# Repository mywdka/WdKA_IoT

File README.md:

# WdKA_IoT
WdKA Internet of Things Repository

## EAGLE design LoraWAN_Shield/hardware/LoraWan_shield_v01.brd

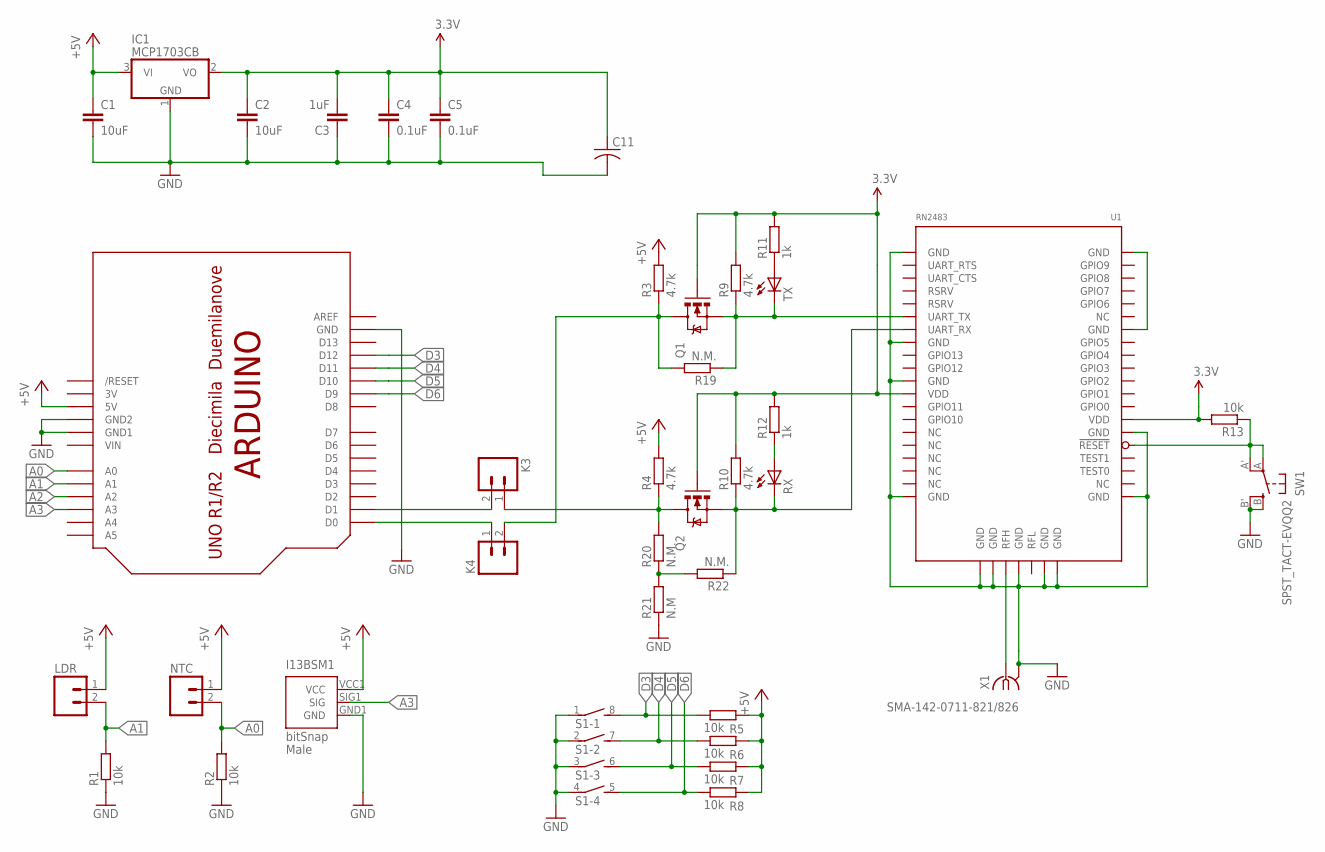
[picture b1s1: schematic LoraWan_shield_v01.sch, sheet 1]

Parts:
ARD1: ARDUINO-NOHOLE
C1, C2: 10uF; C0603K
C3: 1uF; C0603K
C4, C5: 0.1uF; C0603K
C11: C-USC0603; C0603
I13BSM1: BITSNAP_V03_MALE
IC1: MCP1703CB; SOT23
K3, K4: M02LOCK_LONGPADS; 1X02_LOCK_LONGPADS
LDR: M02LOCK_LONGPADS; 1X02_LOCK_LONGPADS
NTC: M02LOCK_LONGPADS; 1X02_LOCK_LONGPADS
Q1, Q2: DMG1012T; SOT523
R1, R2, R5, R6, R7, R8, R13: 10k; R0603
R3, R4, R9, R10: 4.7k; R0603
R11, R12: 1k; R0603
R19, R20, R22: N.M.; R0603
R21: N.M; R0603
RX: LEDCHIPLED_0603; CHIPLED_0603
S1: DIP04S
SW1: SPST_TACT-EVQQ2; EVQ-Q2
TX: LEDCHIPLED_0603; CHIPLED_0603
U1: RN2483
X1: SMA-142-0711-821/826; J502-ND-142-0711-821/826

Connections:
3.3V: C2.1, C3.2, C4.1, C5.1, C11.1, IC1.2 (VO), Q1.1 (G), Q2.1 (G), R9.2, R10.2, R11.2, R12.2, R13.2, U1.12 (VDD), U1.34 (VDD)
3V: ARD1.3V
+5V: ARD1.5V, C1.1, I13BSM1.VCC1 (VCC), IC1.3 (VI), LDR.1, NTC.1, R3.2, R4.2, R5.2, R6.2, R7.2, R8.2; also elsewhere on the board
A0: ARD1.A0, NTC.2, R2.2
A1: ARD1.A1, LDR.2, R1.2
A2: ARD1.A2; also elsewhere on the board
A3: ARD1.A3, I13BSM1.SIG1 (SIG)
ARD_RX: ARD1.D1, K3.2
ARD_TX: ARD1.D0, K4.1
D3: ARD1.D12, R5.1, S1.8 (2)
D4: ARD1.D11, R6.1, S1.7 (2)
D5: ARD1.D10, R7.1, S1.6 (2)
D6: ARD1.D9, R8.1, S1.5 (2)
GND: ARD1.GND, ARD1.GND1, ARD1.GND2, C1.2, C2.2, C3.1, C4.2, C5.2, C11.2, I13BSM1.GND1 (GND), IC1.1 (GND), R1.1, R2.1, R21.1, S1.1, S1.2 (1), S1.3 (1), S1.4 (1), SW1.B (S), SW1.B' (S1), U1.1 (GND), U1.8 (GND), U1.11 (GND), U1.20 (GND), U1.21 (GND), U1.22 (GND), U1.24 (GND), U1.26 (GND), U1.27 (GND), U1.28 (GND), U1.33 (GND), X1.G@1 (2), X1.G@2 (2), X1.G@3 (2), X1.G@4 (2); also elsewhere on the board
unnamed: U1.41 (GND), U1.47 (GND)
unnamed: R13.1, SW1.A, SW1.A' (P1), U1.32 (!RESET!)
unnamed: Q1.2 (S), R9.1, R19.1, TX.C, U1.6 (UART_TX)
unnamed: K4.2, Q1.3 (D), R3.1, R19.2
unnamed: R11.1, TX.A
unnamed: K3.1, Q2.3 (D), R4.1, R20.2
unnamed: R12.1, RX.A
unnamed: U1.23 (RFH), X1.1
unnamed: Q2.2 (S), R10.1, R22.1, RX.C, U1.7 (UART_RX)
unnamed: R20.1, R21.2, R22.2
VIN: ARD1.VIN

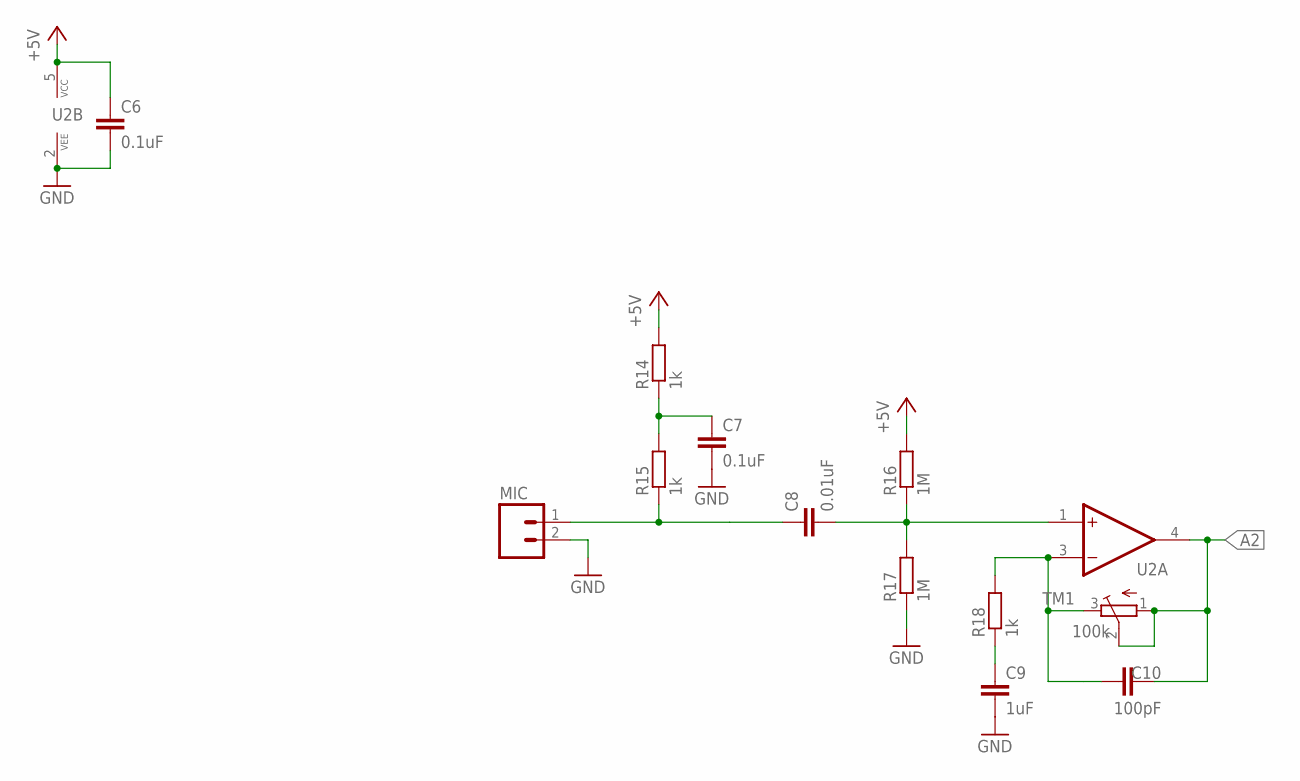
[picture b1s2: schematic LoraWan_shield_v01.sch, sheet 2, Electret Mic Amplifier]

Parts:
C6, C7: 0.1uF; C0603K
C8: 0.01uF; C0603K
C9: 1uF; C0603K
C10: 100pF; C0603K
MIC: M02LOCK_LONGPADS; 1X02_LOCK_LONGPADS
R14, R15, R18: 1k; R0603
R16, R17: 1M; R0603
TM1: 100k; TC33X
U2: MAX4466EXK+T; SC70

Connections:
+5V: C6.1, R14.2, R16.2, U2.5 (VCC); also elsewhere on the board
A2: C10.2, TM1.1 (A), TM1.2 (S), U2.4 (OUT); also elsewhere on the board
GND: C6.2, C7.2, C9.2, MIC.2, R17.1, U2.2 (VEE); also elsewhere on the board
unnamed: C8.1, MIC.1, R15.1
unnamed: C7.1, R14.1, R15.2
unnamed: C9.1, R18.1
unnamed: C8.2, R16.1, R17.2, U2.1 (+IN)
unnamed: C10.1, R18.2, TM1.3 (E), U2.3 (-IN)

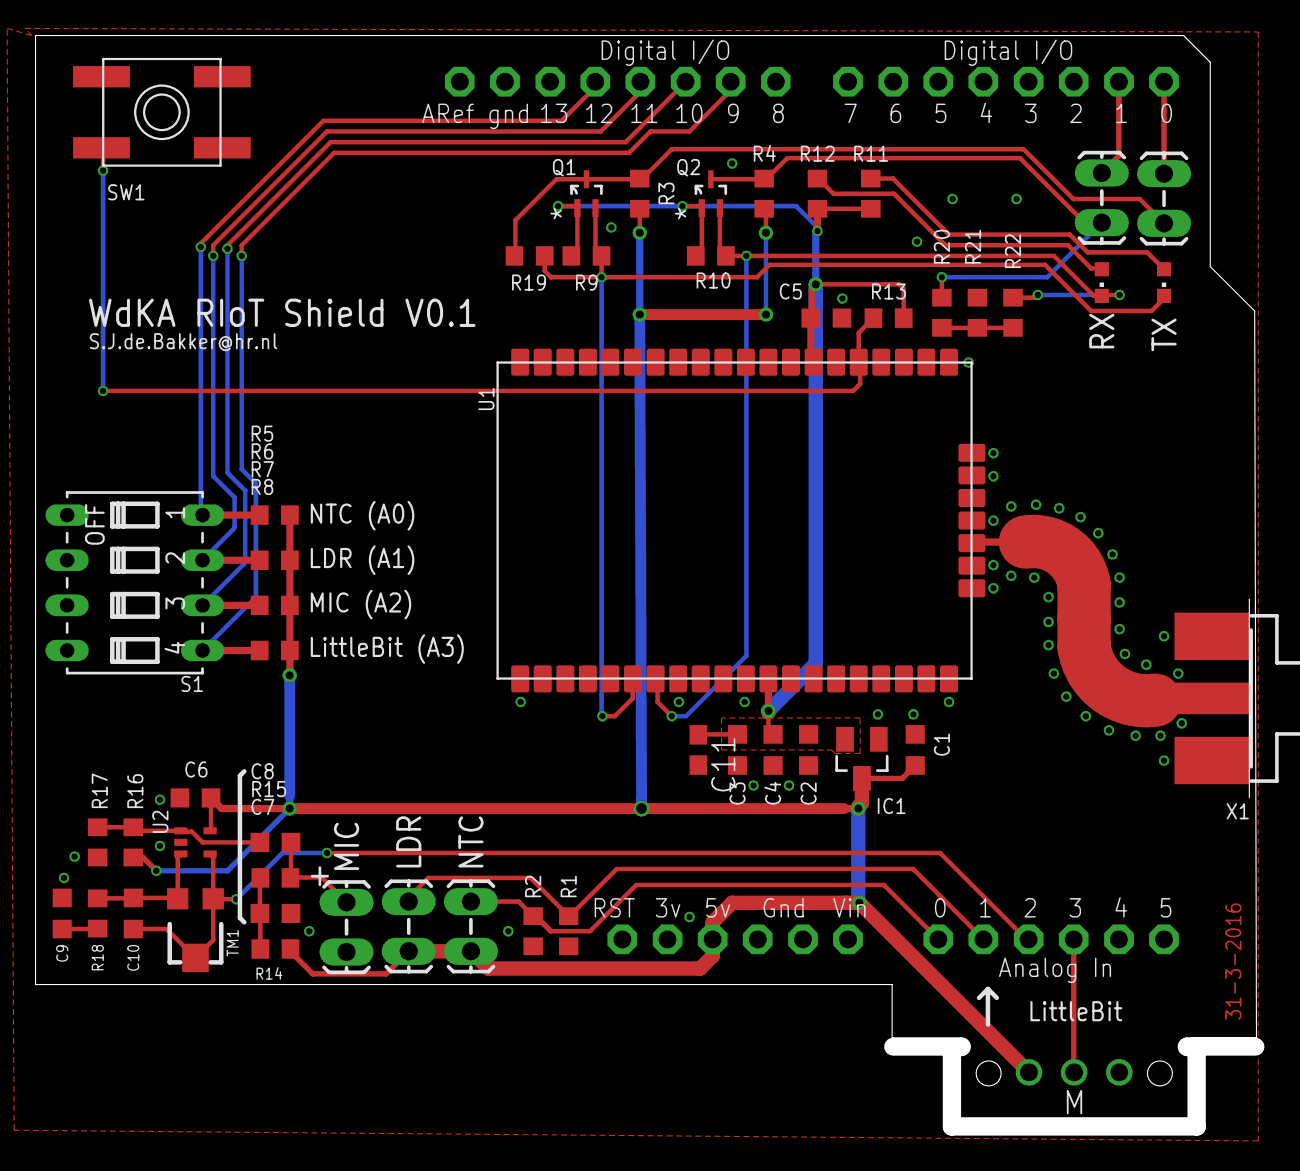
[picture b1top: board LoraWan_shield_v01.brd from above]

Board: 2 copper layers, 68.2 x 60.9 mm, 51 parts (0 on the bottom side), 28 nets.

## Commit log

2016-06-06 Initial commit LoraWan Shiel
2016-06-06 updated .gitignore to contain eagle lock files
2017-04-10 added png of sheets and board
2017-04-18 Removed old version Updated utils program script
